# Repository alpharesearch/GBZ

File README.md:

# GBZ
Gameboy Zero build documentaion.

I got the idea from here: https://www.sudomod.com/wiki/index.php?title=Game_Boy_Zero

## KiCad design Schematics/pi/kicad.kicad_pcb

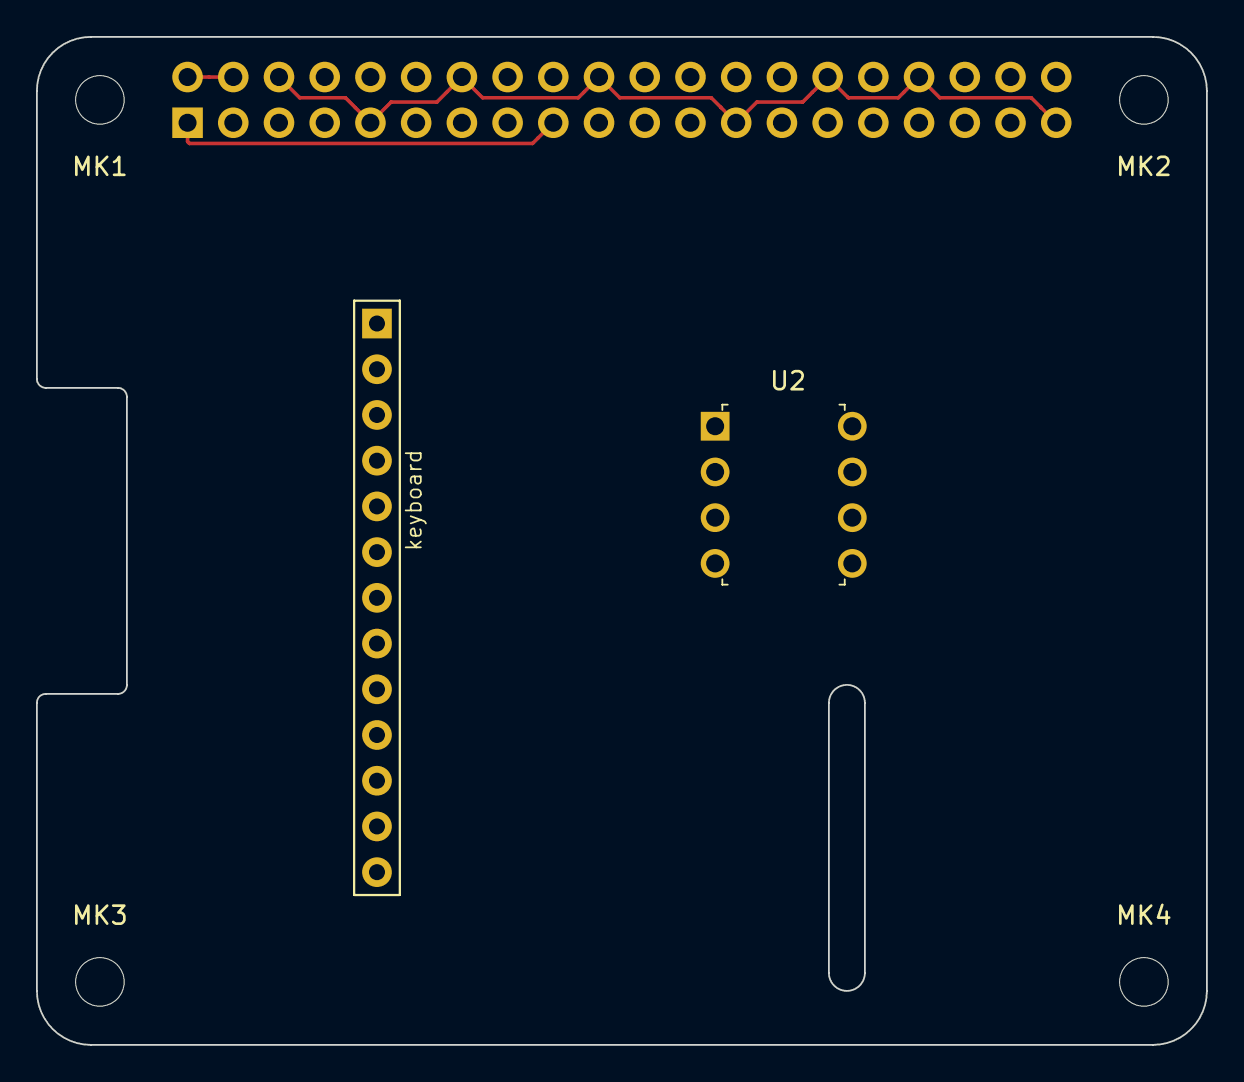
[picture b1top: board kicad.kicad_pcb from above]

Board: 2 copper layers, 65.0 x 56.0 mm, 7 parts (1 on the bottom side), 5 nets.

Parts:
MK1, MK2, MK3, MK4: M2.5; MountingHole_2.7mm_M2.5
P1: Conn_02x20_Odd_Even; PinSocket_2x20_P2.54mm_Vertical
U1: keyboard; H13-2.54
U2: audio; 8-DIP

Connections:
+3V3: P1.1, P1.17
+5V: P1.2, P1.4, U2.2
/GPIO13(PWM1): P1.33, U2.1
/GPIO18(GEN1)(PWM0): P1.12, U2.4
GND: P1.6, P1.9, P1.14, P1.20, P1.25, P1.30, P1.34, P1.39, U1.13, U2.3

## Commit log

2018-04-18 stated on BOM
2018-05-24 add info
2018-05-25 update2
2018-05-27 stated on BOM
    # Conflicts:
    # BOM/bom.ods
